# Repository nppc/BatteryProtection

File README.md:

# Protection circuit for 5S LiIon Battery
The battery is used in mine grass trimmer.

The protection circuit monitoring battery voltage and turns load off if battery gets empty.

Maximum input voltage is 23V.

Low voltage threshold is 15v.

Please make sure, that if your internal reference is 1.1v, then R3 is 68K, not 12K. 12K is for 5V reference.

## Components placement

## Indication
When led blinks with long pauses, then battery is not empty.

When led is constantly on then battery is empty, load is disconnected. To reset the board you need to disconnect the battery.

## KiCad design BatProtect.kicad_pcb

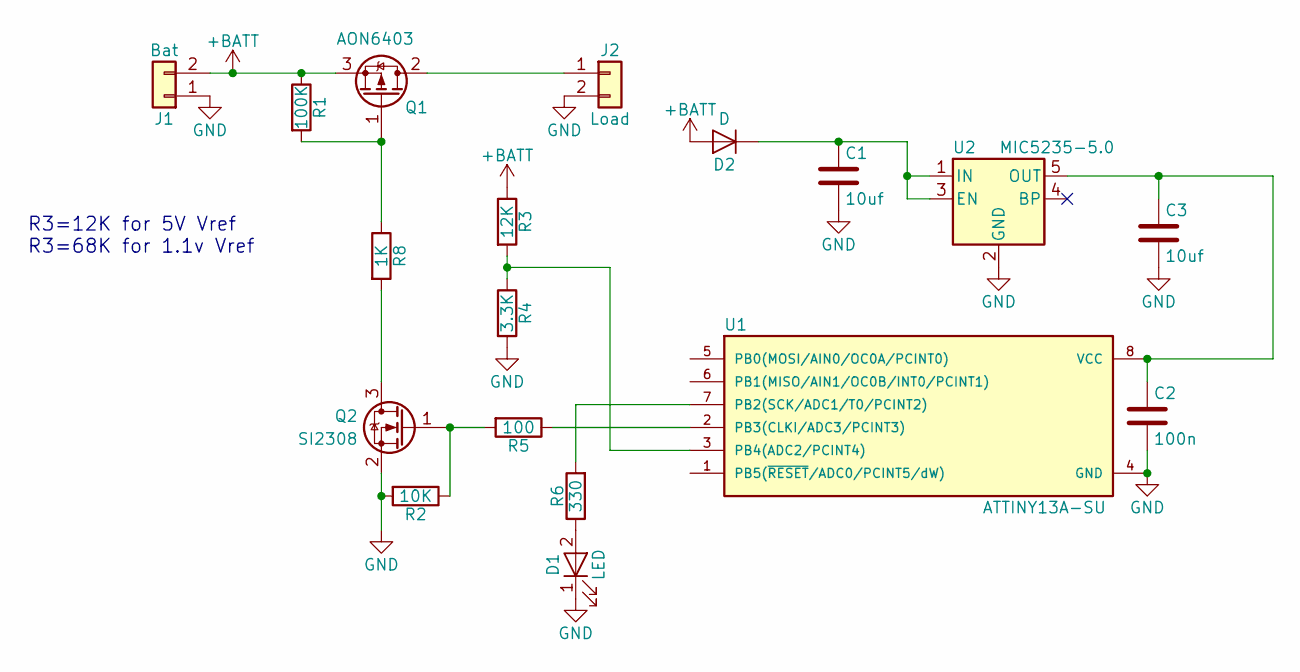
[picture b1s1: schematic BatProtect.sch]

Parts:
C1, C3: 10uf; C_0603
C2: 100n; C_0603
D1: LED; LED_0805
D2: D; D_SOD-323_HandSoldering
J1: Bat; Connector_2x5mm_1.5Drill
J2: Load; Connector_2x5mm_1.5Drill
Q1: AON6403; DFN-8-1EP_6x5mm
Q2: SI2308; SOT-23
R1: 100K; R_0603
R2: 10K; R_0603
R3: 12K; R_0603
R4: 3.3K; R_0603
R5: 100; R_0603
R6: 330; R_0603
R8: 1K; R_0603
U1: ATTINY13A-SU; SOIC-8_3.9x4.9mm_Pitch1.27mm
U2: MIC5235-5.0; SOT-23-5

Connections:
+BATT: D2.2 (A), J1.2, Q1.3 (S), R1.1, R3.1
GND: C1.2, C2.2, C3.2, D1.1 (K), J1.1, J2.2, Q2.2 (S), R2.2, R4.2, U1.4 (GND), U2.2 (GND)
unnamed: C1.1, D2.1 (K), U2.1 (IN), U2.3 (EN)
unnamed: C2.1, C3.1, U1.8 (VCC), U2.5 (OUT)
unnamed: D1.2 (A), R6.1
unnamed: J2.1, Q1.2 (D)
unnamed: Q1.1 (G), R1.2, R8.1
unnamed: Q2.1 (G), R2.1, R5.2
unnamed: Q2.3 (D), R8.2
unnamed: R3.2, R4.1, U1.3 (PB4(ADC2/PCINT4))
unnamed: R5.1, U1.2 (PB3(CLKI/ADC3/PCINT3))
unnamed: R6.2, U1.7 (PB2(SCK/ADC1/T0/PCINT2))

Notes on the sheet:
R3=12K for 5V Vref R3=68K for 1.1v Vref

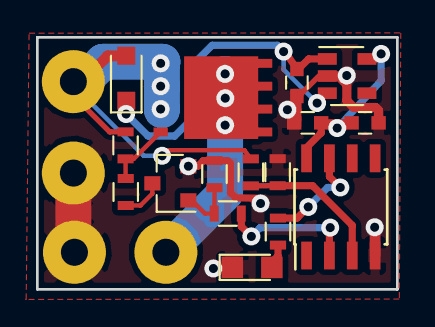
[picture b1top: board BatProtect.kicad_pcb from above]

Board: 2 copper layers, 20.0 x 14.0 mm, 18 parts (0 on the bottom side), 12 nets.

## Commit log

2017-10-18 Adjust wierd problem in schematic and add firmware
2017-10-18 Correct another wierd error
2017-10-19 Some fixes and logic changes
2017-10-19 Again wierd bug in the schematic fixed
2017-10-31 Adjust a bit schematic. Correct resistor divider
2017-10-31 make hex
2017-11-09 ADC Vref changed from 5V to 1.1V
2018-05-09 Changed the mosfet to better one. PCB redesign
2018-05-25 Readme
2018-05-25 Adjust resistor value to get safe Vgs
